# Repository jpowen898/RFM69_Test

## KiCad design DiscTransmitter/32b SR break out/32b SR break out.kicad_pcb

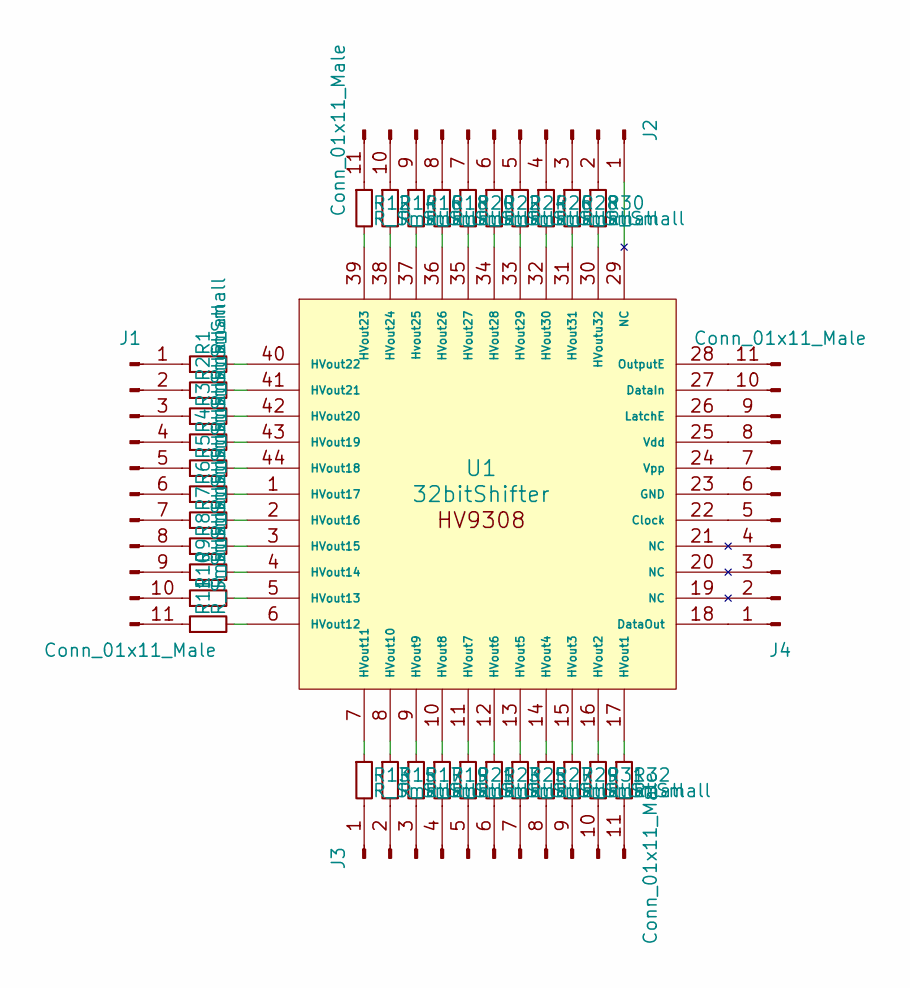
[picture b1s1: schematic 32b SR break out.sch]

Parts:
J1, J2, J3, J4: Conn_01x11_Male; Socket_Strip_Straight_1x11_Pitch2.54mm
R1, R2, R3, R4, R5, R6, R7, R8, R9, R10, R11, R12, R13, R14, R15, R16, R17, R18, R19, R20, R21, R22, R23, R24, R25, R26, R27, R28, R29, R30, R31, R32: R_Small; R_0402_NoSilk
U1: 32bitShifter; PLCC-44

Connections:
unnamed: J1.1, R1.1
unnamed: J1.2, R2.1
unnamed: J1.3, R3.1
unnamed: J1.4, R4.1
unnamed: J1.5, R5.1
unnamed: J1.6, R6.1
unnamed: J1.7, R7.1
unnamed: J1.8, R8.1
unnamed: J1.9, R9.1
unnamed: J1.10, R10.1
unnamed: J1.11, R11.1
unnamed: J2.1, U1.29 (NC)
unnamed: J2.2, R30.1
unnamed: J2.3, R28.1
unnamed: J2.4, R26.1
unnamed: J2.5, R24.1
unnamed: J2.6, R22.1
unnamed: J2.7, R20.1
unnamed: J2.8, R18.1
unnamed: J2.9, R16.1
unnamed: J2.10, R14.1
unnamed: J2.11, R12.1
unnamed: J3.1, R13.2
unnamed: J3.2, R15.2
unnamed: J3.3, R17.2
unnamed: J3.4, R19.2
unnamed: J3.5, R21.2
unnamed: J3.6, R23.2
unnamed: J3.7, R25.2
unnamed: J3.8, R27.2
unnamed: J3.9, R29.2
unnamed: J3.10, R31.2
unnamed: J3.11, R32.2
unnamed: J4.1, U1.18 (DataOut)
unnamed: J4.2, U1.19 (NC)
unnamed: J4.3, U1.20 (NC)
unnamed: J4.4, U1.21 (NC)
unnamed: J4.5, U1.22 (Clock)
unnamed: J4.6, U1.23 (GND)
unnamed: J4.7, U1.24 (Vpp)
unnamed: J4.8, U1.25 (Vdd)
unnamed: J4.9, U1.26 (LatchE)
unnamed: J4.10, U1.27 (DataIn)
unnamed: J4.11, U1.28 (OutputE)
unnamed: R1.2, U1.40 (HVout22)
unnamed: R2.2, U1.41 (HVout21)
unnamed: R3.2, U1.42 (HVout20)
unnamed: R4.2, U1.43 (HVout19)
unnamed: R5.2, U1.44 (HVout18)
unnamed: R6.2, U1.1 (HVout17)
unnamed: R7.2, U1.2 (HVout16)
unnamed: R8.2, U1.3 (HVout15)
unnamed: R9.2, U1.4 (HVout14)
unnamed: R10.2, U1.5 (HVout13)
unnamed: R11.2, U1.6 (HVout12)
unnamed: R12.2, U1.39 (HVout23)
unnamed: R13.1, U1.7 (HVout11)
unnamed: R14.2, U1.38 (HVout24)
unnamed: R15.1, U1.8 (HVout10)
unnamed: R16.2, U1.37 (Hvout25)
unnamed: R17.1, U1.9 (HVout9)
unnamed: R18.2, U1.36 (HVout26)
unnamed: R19.1, U1.10 (HVout8)
unnamed: R20.2, U1.35 (HVout27)
unnamed: R21.1, U1.11 (HVout7)
unnamed: R22.2, U1.34 (HVout28)
unnamed: R23.1, U1.12 (HVout6)
unnamed: R24.2, U1.33 (HVout29)
unnamed: R25.1, U1.13 (HVout5)
unnamed: R26.2, U1.32 (HVout30)
unnamed: R27.1, U1.14 (HVout4)
unnamed: R28.2, U1.31 (HVout31)
unnamed: R29.1, U1.15 (HVout3)
unnamed: R30.2, U1.30 (HVoutu32)
unnamed: R31.1, U1.16 (HVout2)
unnamed: R32.1, U1.17 (HVout1)

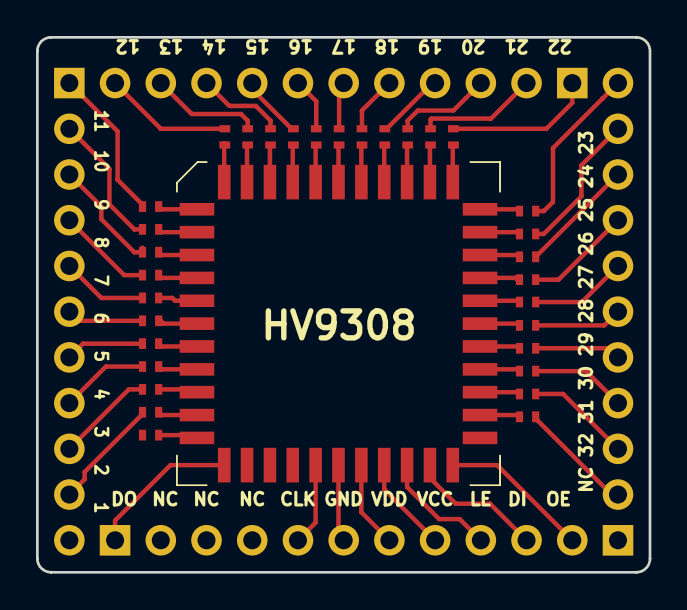
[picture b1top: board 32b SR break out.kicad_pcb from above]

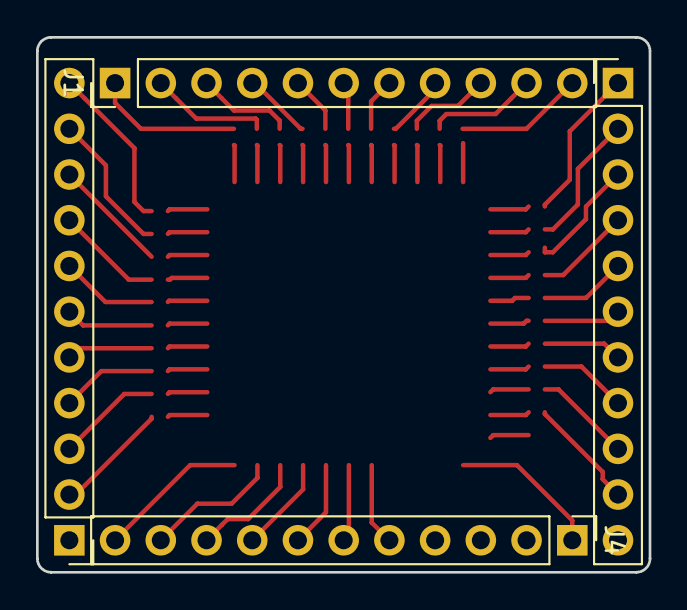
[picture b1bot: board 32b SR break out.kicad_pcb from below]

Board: 2 copper layers, 34.0 x 29.7 mm, 37 parts (4 on the bottom side), 76 nets.

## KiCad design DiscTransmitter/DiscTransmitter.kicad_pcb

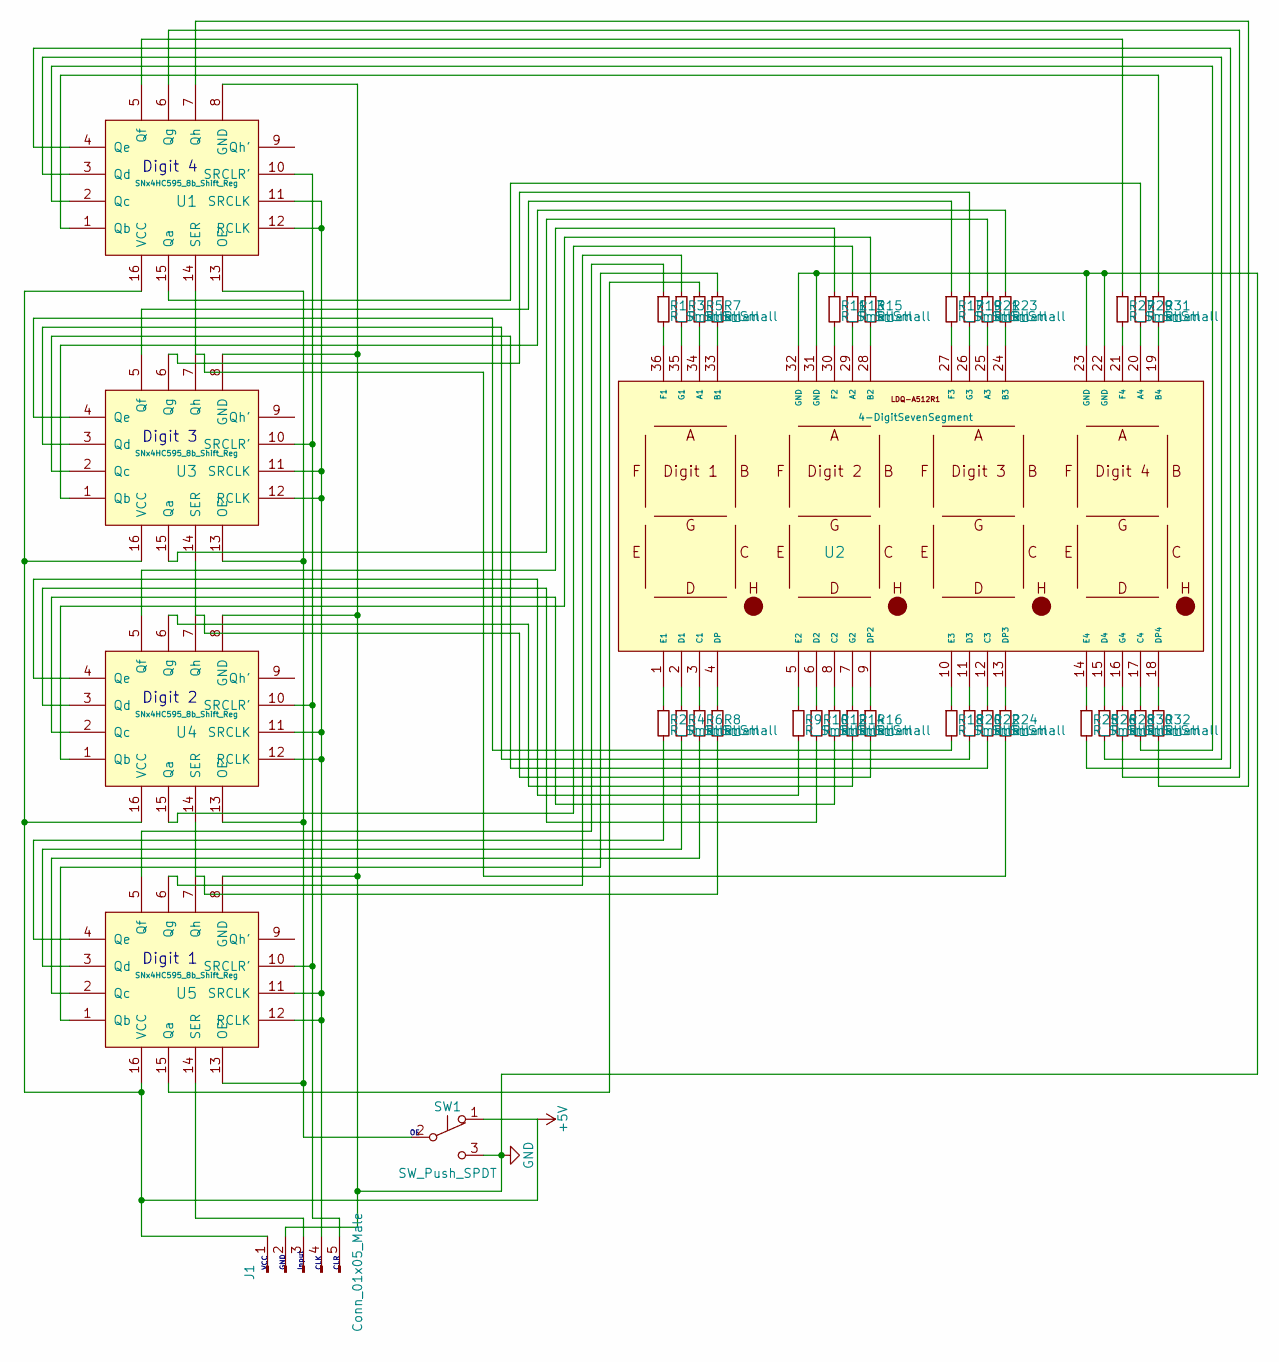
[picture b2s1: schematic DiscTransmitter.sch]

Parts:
J1: Conn_01x05_Male; Socket_Strip_Straight_1x05_Pitch2.54mm
R1, R2, R3, R4, R5, R6, R7, R8, R9, R10, R11, R12, R13, R14, R15, R16, R17, R18, R19, R20, R21, R22, R23, R24, R25, R26, R27, R28, R29, R30, R31, R32: R_Small; R_0201_NoSilk
SW1: SW_Push_SPDT; Socket_Strip_Straight_1x03_Pitch2.54mm
U1, U3, U4, U5: SNx4HC595_8b_Shift_Reg; 8B_Shift_Reg
U2: 4-DigitSevenSegment; FourDigitSevenSegmentDisplay

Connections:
+5V: J1.1, SW1.1 (A), U1.16 (VCC), U3.16 (VCC), U4.16 (VCC), U5.16 (VCC)
GND: J1.2, SW1.3 (C), U1.8 (GND), U2.22 (GND~), U2.23 (GND~), U2.31 (GND~), U2.32 (GND), U3.8 (GND), U4.8 (GND), U5.8 (GND)
unnamed: J1.3, U5.14 (SER)
unnamed: J1.4, U1.11 (SRCLK), U1.12 (RCLK), U3.11 (SRCLK), U3.12 (RCLK), U4.11 (SRCLK), U4.12 (RCLK), U5.11 (SRCLK), U5.12 (RCLK)
unnamed: J1.5, U1.10 (SRCLR'), U3.10 (SRCLR'), U4.10 (SRCLR'), U5.10 (SRCLR')
unnamed: R1.1, U5.5 (Qf)
unnamed: R1.2, U2.36 (F1)
unnamed: R2.1, U2.1 (E1)
unnamed: R2.2, U5.4 (Qe)
unnamed: R3.1, U5.6 (Qg)
unnamed: R3.2, U2.35 (G1)
unnamed: R4.1, U2.2 (D1)
unnamed: R4.2, U5.3 (Qd)
unnamed: R5.1, U5.15 (Qa)
unnamed: R5.2, U2.34 (A1)
unnamed: R6.1, U2.3 (C1)
unnamed: R6.2, U5.2 (Qc)
unnamed: R7.1, U5.1 (Qb)
unnamed: R7.2, U2.33 (B1)
unnamed: R8.1, U2.4 (DP)
unnamed: R8.2, U4.14 (SER), U5.7 (Qh)
unnamed: R9.1, U2.5 (E2)
unnamed: R9.2, U4.4 (Qe)
unnamed: R10.1, U2.6 (D2)
unnamed: R10.2, U4.3 (Qd)
unnamed: R11.1, U4.5 (Qf)
unnamed: R11.2, U2.30 (F2)
unnamed: R12.1, U2.8 (C2)
unnamed: R12.2, U4.2 (Qc)
unnamed: R13.1, U4.15 (Qa)
unnamed: R13.2, U2.29 (A2)
unnamed: R14.1, U2.7 (G2)
unnamed: R14.2, U4.6 (Qg)
unnamed: R15.1, U4.1 (Qb)
unnamed: R15.2, U2.28 (B2)
unnamed: R16.1, U2.9 (DP2)
unnamed: R16.2, U3.14 (SER), U4.7 (Qh)
unnamed: R17.1, U3.5 (Qf)
unnamed: R17.2, U2.27 (F3)
unnamed: R18.1, U2.10 (E3)
unnamed: R18.2, U3.4 (Qe)
unnamed: R19.1, U3.6 (Qg)
unnamed: R19.2, U2.26 (G3)
unnamed: R20.1, U2.11 (D3)
unnamed: R20.2, U3.3 (Qd)
unnamed: R21.1, U3.15 (Qa)
unnamed: R21.2, U2.25 (A3)
unnamed: R22.1, U2.12 (C3)
unnamed: R22.2, U3.2 (Qc)
unnamed: R23.1, U3.1 (Qb)
unnamed: R23.2, U2.24 (B3)
unnamed: R24.1, U2.13 (DP3)
unnamed: R24.2, U1.14 (SER), U3.7 (Qh)
unnamed: R25.1, U2.14 (E4)
unnamed: R25.2, U1.4 (Qe)
unnamed: R26.1, U2.15 (D4)
unnamed: R26.2, U1.3 (Qd)
unnamed: R27.1, U1.5 (Qf)
unnamed: R27.2, U2.21 (F4)
unnamed: R28.1, U2.16 (G4)
unnamed: R28.2, U1.6 (Qg)
unnamed: R29.1, U1.15 (Qa)
unnamed: R29.2, U2.20 (A4)
unnamed: R30.1, U2.17 (C4)
unnamed: R30.2, U1.2 (Qc)
unnamed: R31.1, U1.1 (Qb)
unnamed: R31.2, U2.19 (B4)
unnamed: R32.1, U2.18 (DP4)
unnamed: R32.2, U1.7 (Qh)
unnamed: SW1.2 (B), U1.13 (OE'), U3.13 (OE'), U4.13 (OE'), U5.13 (OE')

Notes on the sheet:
Digit 1
Digit 2
Digit 3
Digit 4
GND
CLK
CLR
Input
VCC

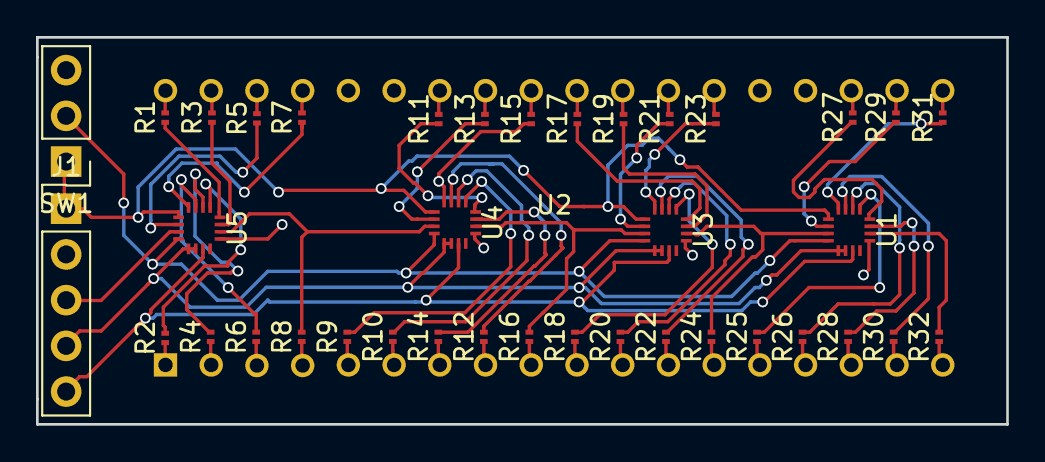
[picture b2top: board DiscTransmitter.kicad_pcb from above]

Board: 2 copper layers, 53.9 x 21.5 mm, 39 parts (0 on the bottom side), 70 nets.

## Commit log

2018-05-11 inital commit
2018-05-11 Added functional test of receiver code
2018-10-22 Deleted the Disc Transmitter Kicad Files since I have another repository with them in it now
2018-12-27 saved
2018-12-27 Outputs an average rssi val based on the last 5 rssi values
2018-12-27 Transmitter: sleep after 100 seconds, brodcast every quarter second Reciever: averages last 5 rssi vals, then scalses them to up by 10
2019-01-05 Takes Average of 7 rssi values (seemed to be the most accurate). Put RFM in sleep mode between transmissions.
2019-01-18 Added interrupt to wake from sleep
2019-01-18 Added an h file with the board specific pinouts on it. I also added a Power Managment class. Sleep is working perfectlu, but DeepSleep is still not waking up from interrupts.
2019-01-23 Partialy complete new Power Management class. Sleep works, but DeepSleep still will not wake up from interrupts.
2019-02-06 Updated pins for new minimized board.
2019-02-06 added an h file for the new board's pins
2019-02-06 Fixed #defines
2019-02-22 Fixing the MPower.h code
2019-03-29 Added 7segment display to show rssi. Isn't working with the transmit receive board yet.
